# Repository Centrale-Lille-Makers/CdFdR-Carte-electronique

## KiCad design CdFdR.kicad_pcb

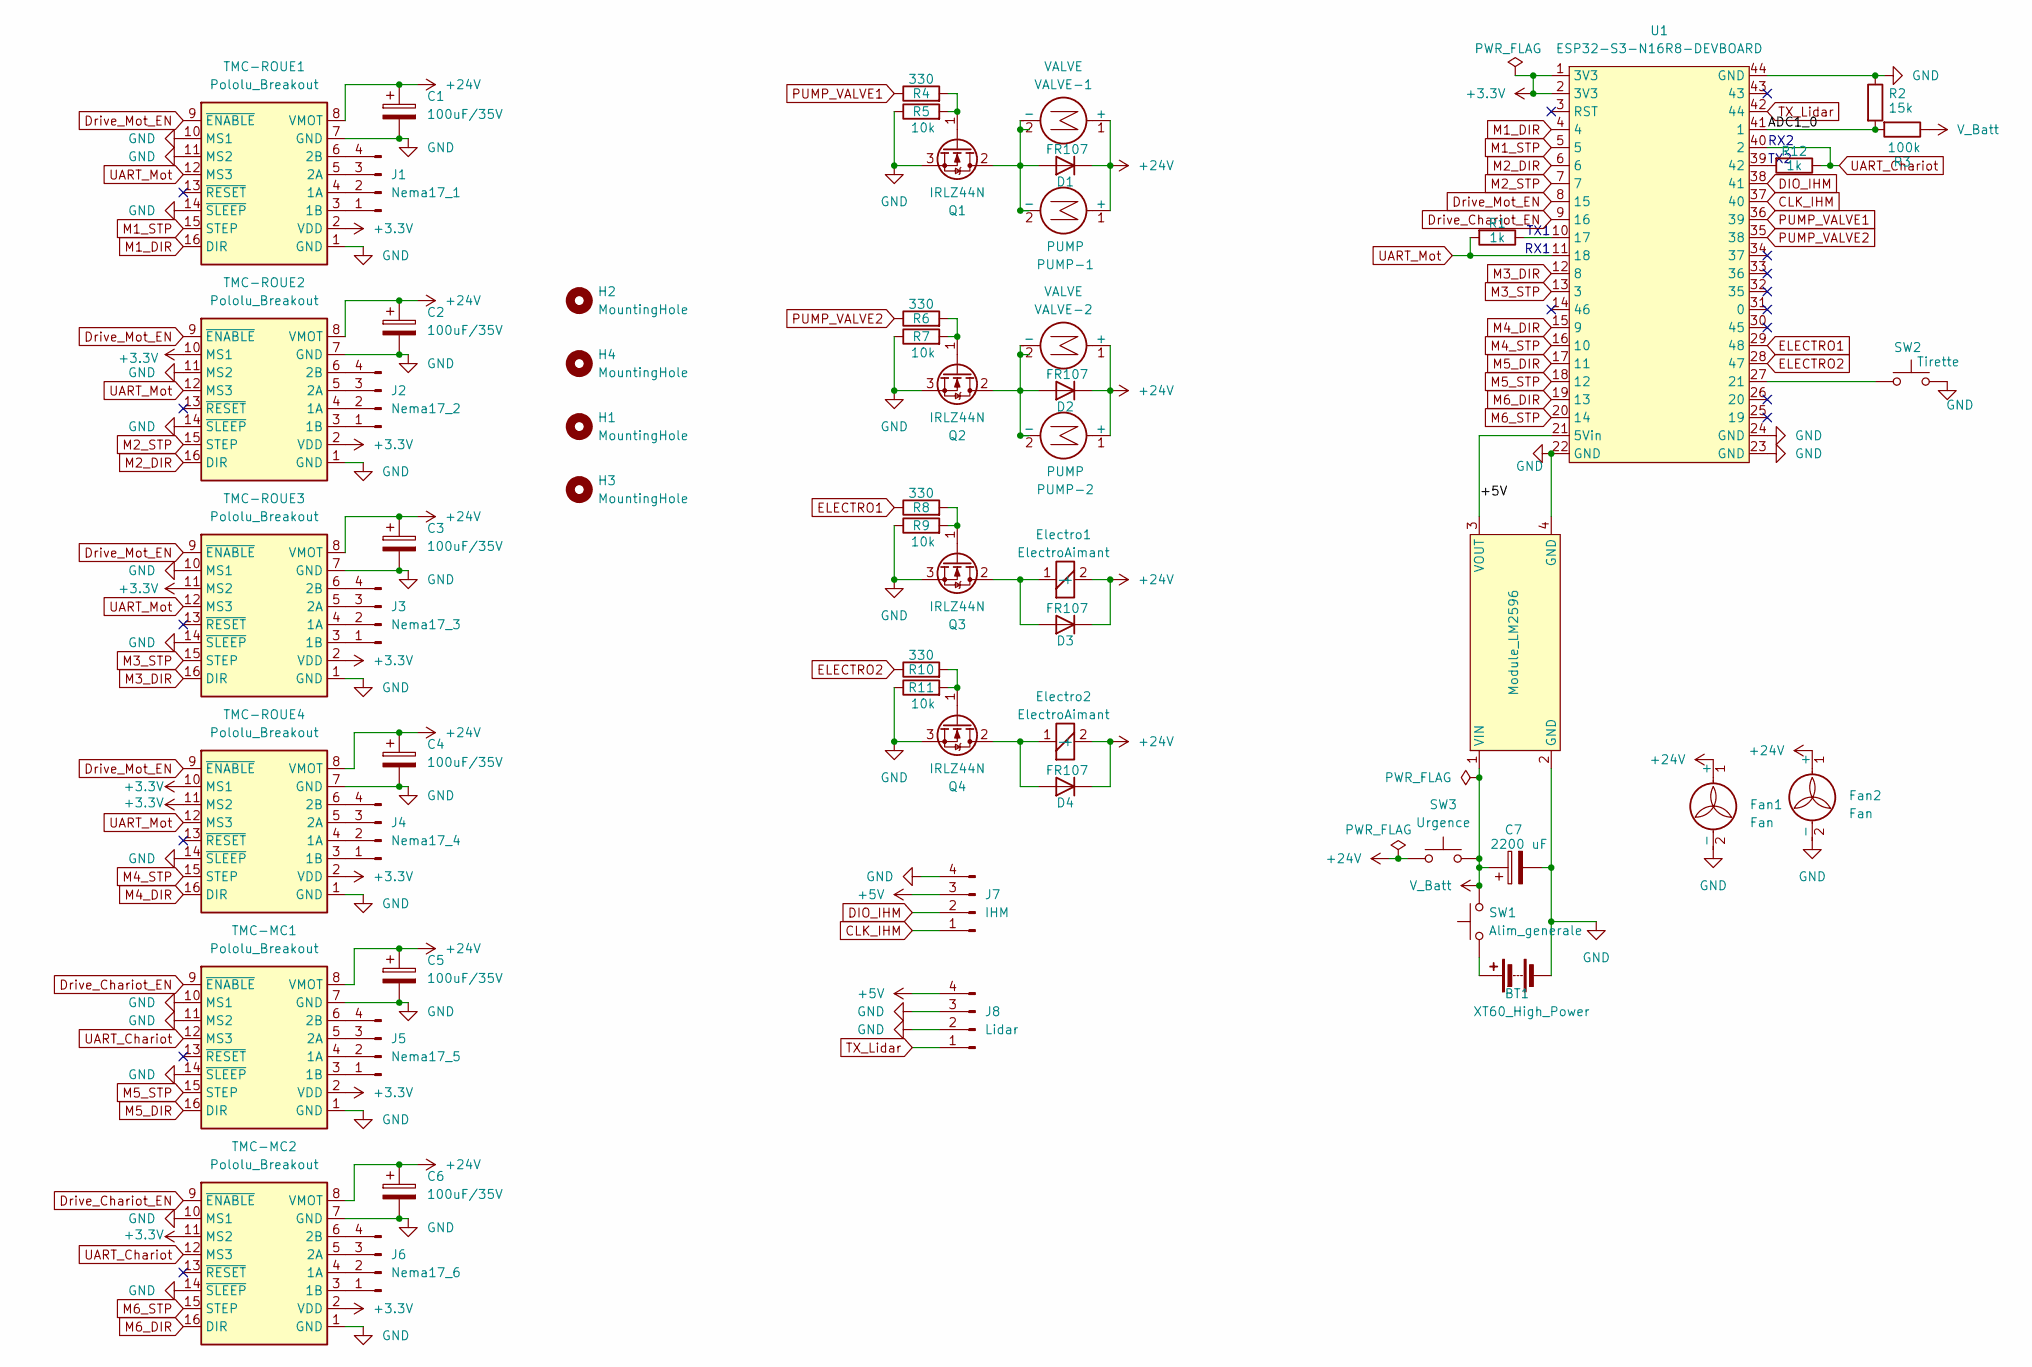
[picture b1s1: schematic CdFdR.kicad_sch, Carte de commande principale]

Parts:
BT1: XT60_High_Power; AMASS_XT60-M_1x02_P7.20mm_Vertical
C1, C2, C3, C4, C5, C6: 100uF/35V; CP_Radial_D6.3mm_P2.50mm
C7: 2200 uF; CP_Radial_D16.0mm_P7.50mm
D1, D2, D3, D4: FR107; D_DO-41_SOD81_P7.62mm_Horizontal
Electro1, Electro2: ElectroAimant; JST_XH_B2B-XH-A_1x02_P2.50mm_Vertical
Fan1, Fan2: Fan; JST_XH_B2B-XH-A_1x02_P2.50mm_Vertical
H1, H2, H3, H4: MountingHole; MountingHole_3.2mm_M3
J1: Nema17_1; JST_XH_B4B-XH-A_1x04_P2.50mm_Vertical
J2: Nema17_2; JST_XH_B4B-XH-A_1x04_P2.50mm_Vertical
J3: Nema17_3; JST_XH_B4B-XH-A_1x04_P2.50mm_Vertical
J4: Nema17_4; JST_XH_B4B-XH-A_1x04_P2.50mm_Vertical
J5: Nema17_5; JST_XH_B4B-XH-A_1x04_P2.50mm_Vertical
J6: Nema17_6; JST_XH_B4B-XH-A_1x04_P2.50mm_Vertical
J7: IHM; JST_XH_B4B-XH-A_1x04_P2.50mm_Vertical
J8: Lidar; JST_XH_B4B-XH-A_1x04_P2.50mm_Vertical
Module_LM2596: LM2596; LM2596 Converter DC-DC
PUMP-1, PUMP-2: PUMP; JST_XH_B2B-XH-A_1x02_P2.50mm_Vertical
Q1, Q2, Q3, Q4: IRLZ44N; TO-220-3_Vertical
R1, R12: 1k; R_Axial_DIN0207_L6.3mm_D2.5mm_P7.62mm_Horizontal
R2: 15k; R_Axial_DIN0207_L6.3mm_D2.5mm_P7.62mm_Horizontal
R3: 100k; R_Axial_DIN0207_L6.3mm_D2.5mm_P7.62mm_Horizontal
R4, R6, R8, R10: 330; R_Axial_DIN0207_L6.3mm_D2.5mm_P7.62mm_Horizontal
R5, R7, R9, R11: 10k; R_Axial_DIN0207_L6.3mm_D2.5mm_P7.62mm_Horizontal
SW1: Alim_generale; AMASS_XT60-F_1x02_P7.20mm_Vertical
SW2: Tirette; JST_XH_B2B-XH-A_1x02_P2.50mm_Vertical
SW3: Urgence; AMASS_XT60-F_1x02_P7.20mm_Vertical
TMC-MC1, TMC-MC2: Pololu_Breakout; Pololu_Breakout-16_15.2x20.3mm_Better_Silkscreen
TMC-ROUE1, TMC-ROUE2, TMC-ROUE3, TMC-ROUE4: Pololu_Breakout; Pololu_Breakout-16_15.2x20.3mm_Better_Silkscreen
U1: ESP32-S3-N16R8-DEVBOARD; ESP32-S3-DevKit
VALVE-1, VALVE-2: VALVE; JST_XH_B2B-XH-A_1x02_P2.50mm_Vertical

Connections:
+3.3V: TMC-MC1.2 (VDD), TMC-MC2.2 (VDD), TMC-MC2.11 (MS2), TMC-ROUE1.2 (VDD), TMC-ROUE2.2 (VDD), TMC-ROUE2.10 (MS1), TMC-ROUE3.2 (VDD), TMC-ROUE3.11 (MS2), TMC-ROUE4.2 (VDD), TMC-ROUE4.10 (MS1), TMC-ROUE4.11 (MS2), U1.1 (3V3), U1.2 (3V3)
+5V: J7.3, J8.4, Module_LM2596.3 (VOUT), U1.21 (5Vin)
+24V: C1.1, C2.1, C3.1, C4.1, C5.1, C6.1, D1.1 (K), D2.1 (K), D3.1 (K), D4.1 (K), Electro1.2 (+), Electro2.2 (+), Fan1.1 (+), Fan2.1 (+), PUMP-1.1 (+), PUMP-2.1 (+), SW3.1, TMC-MC1.8 (VMOT), TMC-MC2.8 (VMOT), TMC-ROUE1.8 (VMOT), TMC-ROUE2.8 (VMOT), TMC-ROUE3.8 (VMOT), TMC-ROUE4.8 (VMOT), VALVE-1.1 (+), VALVE-2.1 (+)
/ADC1_0: R2.2, R3.2, U1.41 (1)
CLK_IHM: J7.1, U1.37 (40)
DIO_IHM: J7.2, U1.38 (41)
Drive_Chariot_EN: TMC-MC1.9 (~ENABLE), TMC-MC2.9 (~ENABLE), U1.9 (16)
Drive_Mot_EN: TMC-ROUE1.9 (~ENABLE), TMC-ROUE2.9 (~ENABLE), TMC-ROUE3.9 (~ENABLE), TMC-ROUE4.9 (~ENABLE), U1.8 (15)
ELECTRO1: R8.1, U1.29 (48)
ELECTRO2: R10.1, U1.28 (47)
GND: BT1.2 (-), C1.2, C2.2, C3.2, C4.2, C5.2, C6.2, C7.2, Fan1.2 (-), Fan2.2 (-), J7.4, J8.2, J8.3, Module_LM2596.2 (GND), Module_LM2596.4 (GND), Q1.3 (S), Q2.3 (S), Q3.3 (S), Q4.3 (S), R2.1, R5.1, R7.1, R9.1, R11.1, SW2.2, TMC-MC1.1 (GND), TMC-MC1.7 (GND), TMC-MC1.10 (MS1), TMC-MC1.11 (MS2), TMC-MC1.14 (~SLEEP), TMC-MC2.1 (GND), TMC-MC2.7 (GND), TMC-MC2.10 (MS1), TMC-MC2.14 (~SLEEP), TMC-ROUE1.1 (GND), TMC-ROUE1.7 (GND), TMC-ROUE1.10 (MS1), TMC-ROUE1.11 (MS2), TMC-ROUE1.14 (~SLEEP), TMC-ROUE2.1 (GND), TMC-ROUE2.7 (GND), TMC-ROUE2.11 (MS2), TMC-ROUE2.14 (~SLEEP), TMC-ROUE3.1 (GND), TMC-ROUE3.7 (GND), TMC-ROUE3.10 (MS1), TMC-ROUE3.14 (~SLEEP), TMC-ROUE4.1 (GND), TMC-ROUE4.7 (GND), TMC-ROUE4.14 (~SLEEP), U1.22 (GND), U1.23 (GND), U1.24 (GND), U1.44 (GND)
M1_DIR: TMC-ROUE1.16 (DIR), U1.4
M1_STP: TMC-ROUE1.15 (STEP), U1.5
M2_DIR: TMC-ROUE2.16 (DIR), U1.6
M2_STP: TMC-ROUE2.15 (STEP), U1.7
M3_DIR: TMC-ROUE3.16 (DIR), U1.12 (8)
M3_STP: TMC-ROUE3.15 (STEP), U1.13 (3)
M4_DIR: TMC-ROUE4.16 (DIR), U1.15 (9)
M4_STP: TMC-ROUE4.15 (STEP), U1.16 (10)
M5_DIR: TMC-MC1.16 (DIR), U1.17 (11)
M5_STP: TMC-MC1.15 (STEP), U1.18 (12)
M6_DIR: TMC-MC2.16 (DIR), U1.19 (13)
M6_STP: TMC-MC2.15 (STEP), U1.20 (14)
unnamed: BT1.1 (+), SW1.1
unnamed: D1.2 (A), PUMP-1.2 (-), Q1.2 (D), VALVE-1.2 (-)
unnamed: D2.2 (A), PUMP-2.2 (-), Q2.2 (D), VALVE-2.2 (-)
unnamed: D3.2 (A), Electro1.1 (-), Q3.2 (D)
unnamed: D4.2 (A), Electro2.1 (-), Q4.2 (D)
unnamed: J1.1, TMC-ROUE1.3 (1B)
unnamed: J1.2, TMC-ROUE1.4 (1A)
unnamed: J1.3, TMC-ROUE1.5 (2A)
unnamed: J1.4, TMC-ROUE1.6 (2B)
unnamed: J2.1, TMC-ROUE2.3 (1B)
unnamed: J2.2, TMC-ROUE2.4 (1A)
unnamed: J2.3, TMC-ROUE2.5 (2A)
unnamed: J2.4, TMC-ROUE2.6 (2B)
unnamed: J3.1, TMC-ROUE3.3 (1B)
unnamed: J3.2, TMC-ROUE3.4 (1A)
unnamed: J3.3, TMC-ROUE3.5 (2A)
unnamed: J3.4, TMC-ROUE3.6 (2B)
unnamed: J4.1, TMC-ROUE4.3 (1B)
unnamed: J4.2, TMC-ROUE4.4 (1A)
unnamed: J4.3, TMC-ROUE4.5 (2A)
unnamed: J4.4, TMC-ROUE4.6 (2B)
unnamed: J5.1, TMC-MC1.3 (1B)
unnamed: J5.2, TMC-MC1.4 (1A)
unnamed: J5.3, TMC-MC1.5 (2A)
unnamed: J5.4, TMC-MC1.6 (2B)
unnamed: J6.1, TMC-MC2.3 (1B)
unnamed: J6.2, TMC-MC2.4 (1A)
unnamed: J6.3, TMC-MC2.5 (2A)
unnamed: J6.4, TMC-MC2.6 (2B)
unnamed: Q1.1 (G), R4.2, R5.2
unnamed: Q2.1 (G), R6.2, R7.2
unnamed: Q3.1 (G), R8.2, R9.2
unnamed: Q4.1 (G), R10.2, R11.2
unnamed: R1.1, U1.10 (17)
unnamed: SW2.1, U1.27 (21)
unnamed: R12.2, U1.39 (42)
PUMP_VALVE1: R4.1, U1.36 (39)
PUMP_VALVE2: R6.1, U1.35 (38)
TX_Lidar: J8.1, U1.42 (44)
UART_Chariot: R12.1, TMC-MC1.12 (MS3), TMC-MC2.12 (MS3), U1.40 (2)
UART_Mot: R1.2, TMC-ROUE1.12 (MS3), TMC-ROUE2.12 (MS3), TMC-ROUE3.12 (MS3), TMC-ROUE4.12 (MS3), U1.11 (18)
V_Batt: C7.1, Module_LM2596.1 (VIN), R3.1, SW1.2, SW3.2

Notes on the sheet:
TX2
RX1
TX1
RX2

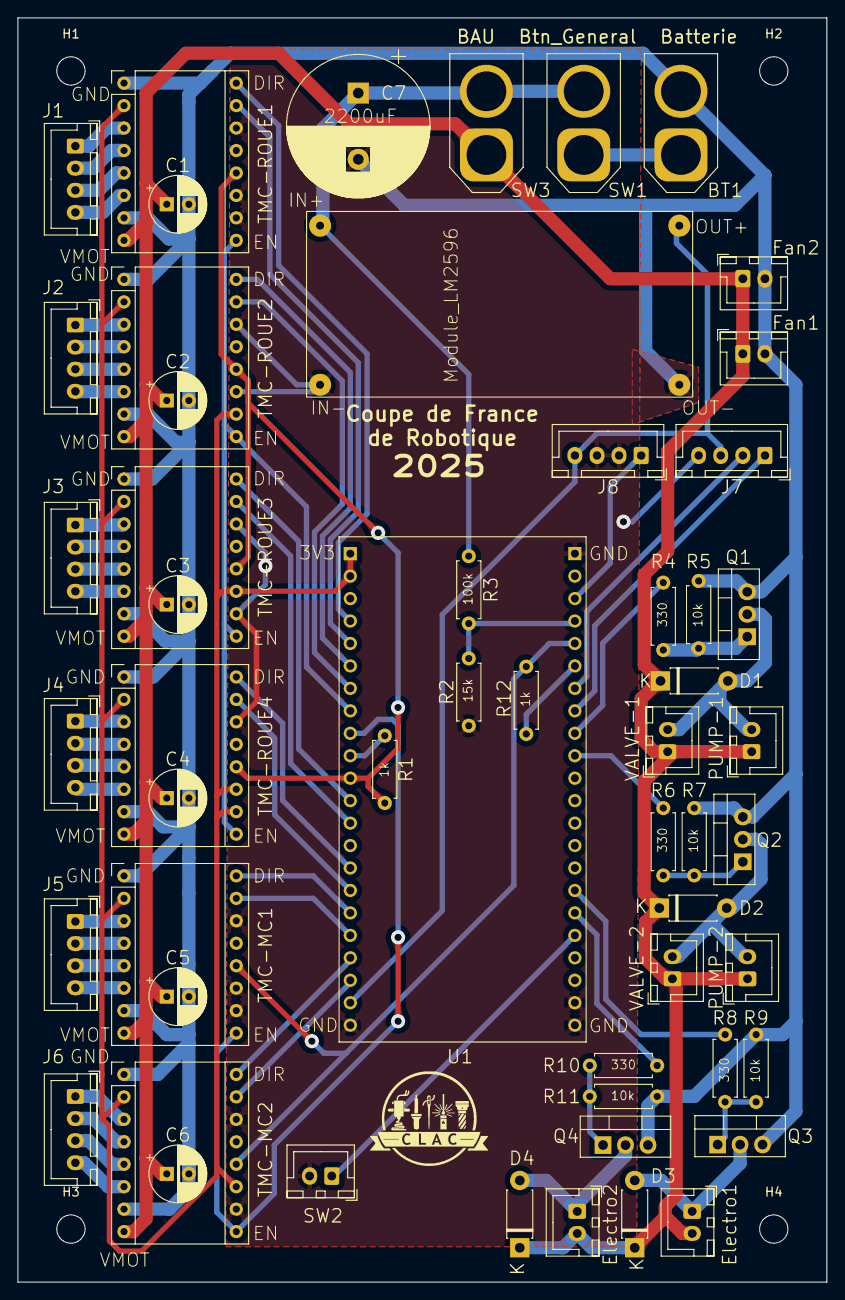
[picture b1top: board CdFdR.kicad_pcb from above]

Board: 2 copper layers, 91.5 x 143.0 mm, 59 parts (0 on the bottom side), 65 nets.

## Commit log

2025-01-27 Rev .1
2025-02-14 Changed drivers uart code due to error on hand soldered board
2025-02-15 Correction des pins des moteurs pour être en accord avec carte soudé
2025-05-05 Ajout de composants
    Ajout de composants sur le schématic
2025-05-13 Version envoyé pour vérif
2025-05-15 Ajout de teardrops
2025-05-16 Config pour commande
